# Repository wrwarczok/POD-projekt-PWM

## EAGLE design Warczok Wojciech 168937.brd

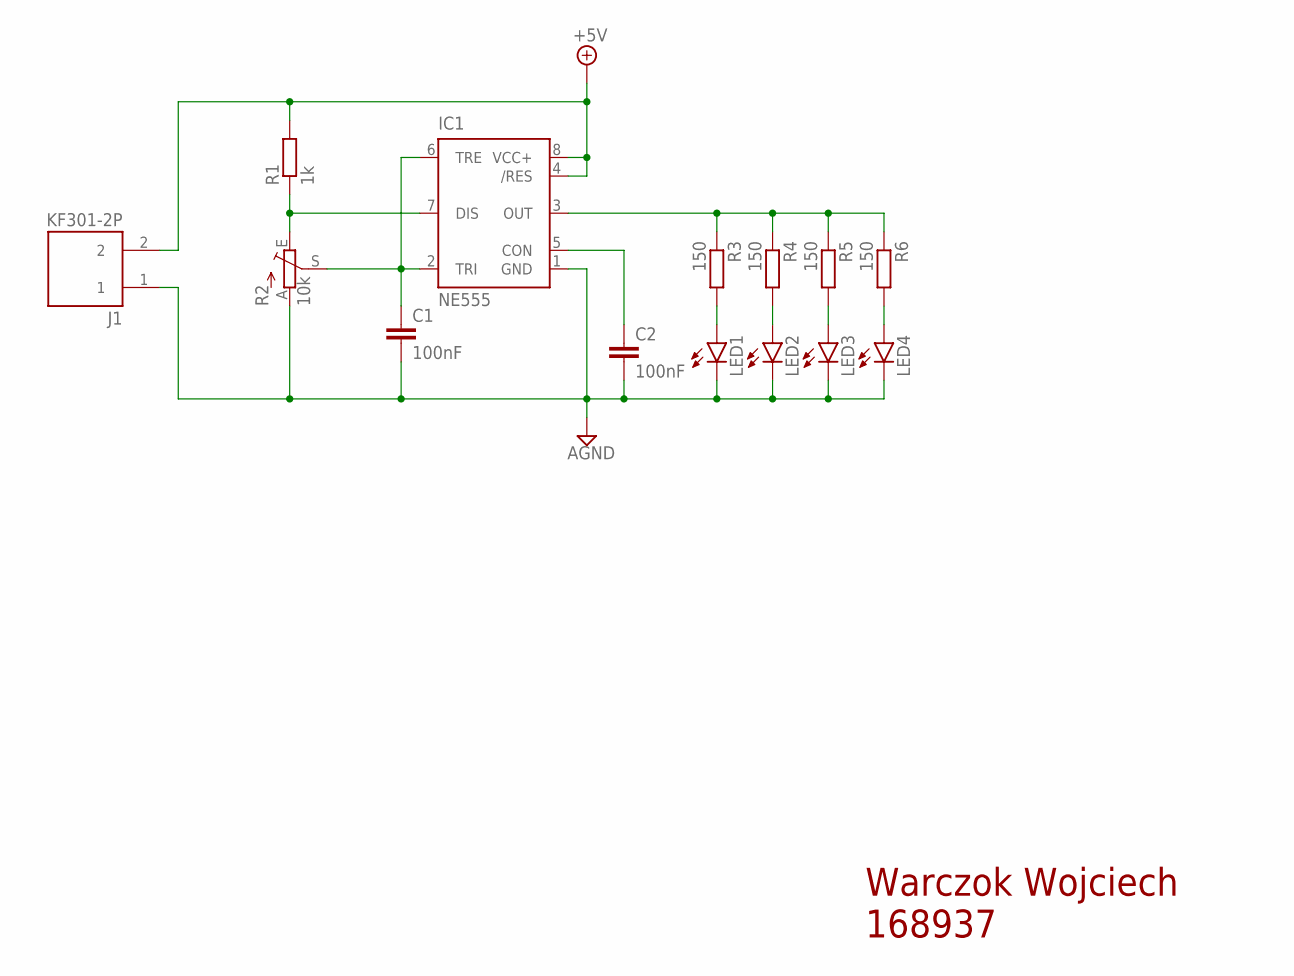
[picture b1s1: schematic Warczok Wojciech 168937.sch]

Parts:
C1, C2: 100nF; C025-024X044
IC1: NE555; DIL-08
J1: KF301-2P; HANDSON_KF301-2P
LED1, LED2, LED3, LED4: LED5MM
R1: 1k; 0204/7
R2: 10k; CA6V
R3, R4, R5, R6: 150; 0204/7

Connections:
+5V: IC1.4 (/RES), IC1.8 (VCC+), J1.2, R1.2
AGND: C1.2, C2.2, IC1.1 (GND), J1.1, LED1.K (C), LED2.K (C), LED3.K (C), LED4.K (C), R2.A
unnamed: C1.1, IC1.2 (TRI), IC1.6 (TRE), R2.S
unnamed: IC1.3 (OUT), R3.1, R4.1, R5.1, R6.1
unnamed: IC1.7 (DIS), R1.1, R2.E
unnamed: C2.1, IC1.5 (CON)
unnamed: LED1.A, R3.2
unnamed: LED2.A, R4.2
unnamed: LED3.A, R5.2
unnamed: LED4.A, R6.2

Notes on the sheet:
Warczok Wojciech 168937

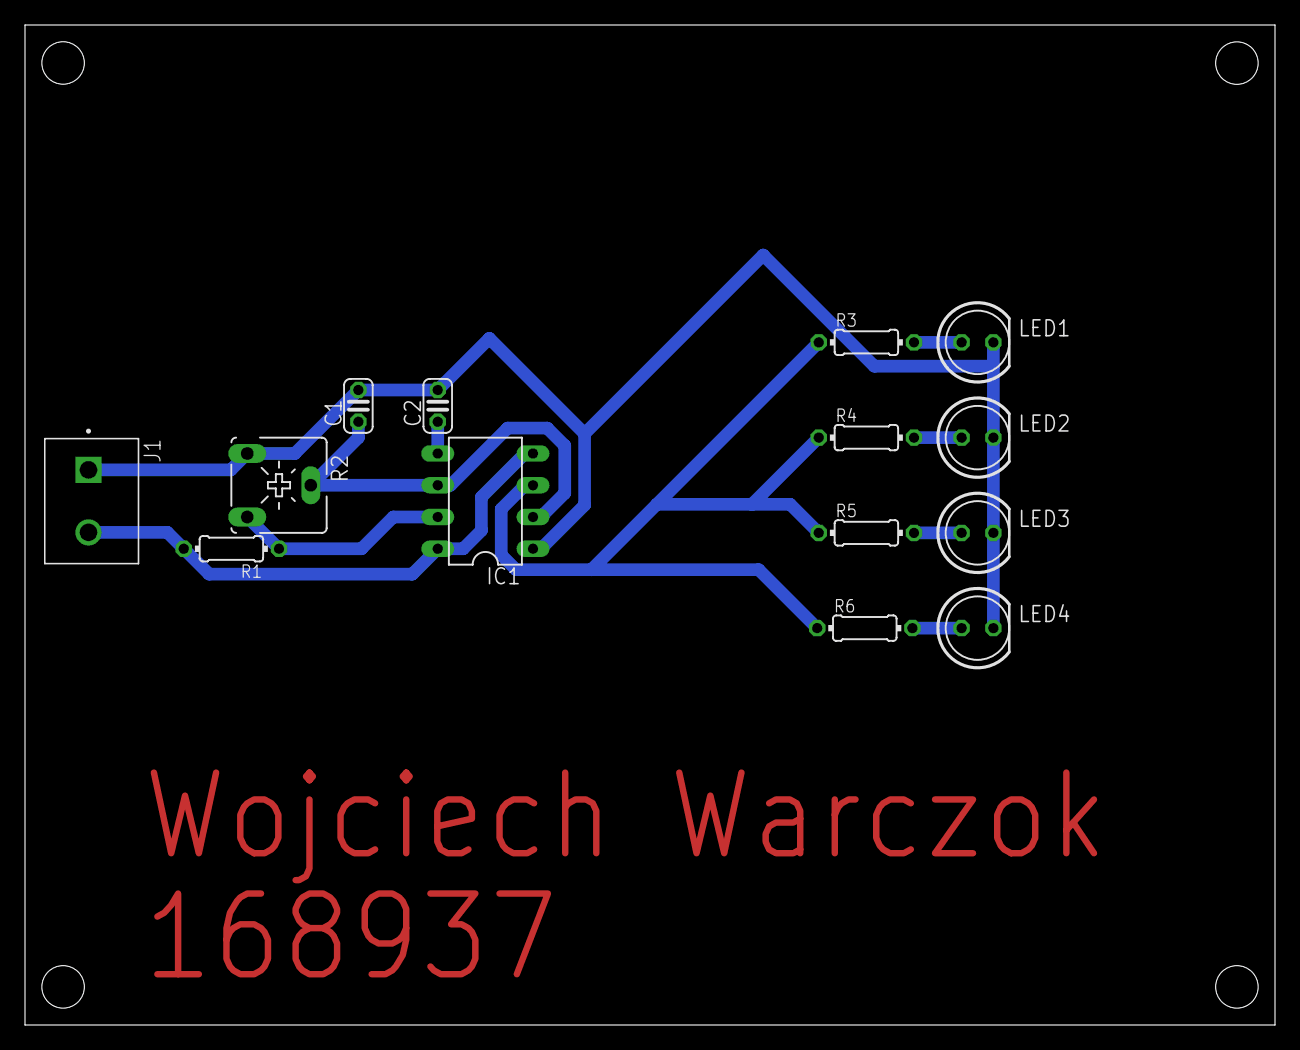
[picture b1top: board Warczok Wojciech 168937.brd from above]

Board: 2 copper layers, 100.0 x 80.0 mm, 14 parts (0 on the bottom side), 10 nets.
